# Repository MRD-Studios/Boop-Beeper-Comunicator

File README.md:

# Boop Beeper Comunicator
A Pico Pi & LoRa communicator built on micropython. (The name is not final)

##

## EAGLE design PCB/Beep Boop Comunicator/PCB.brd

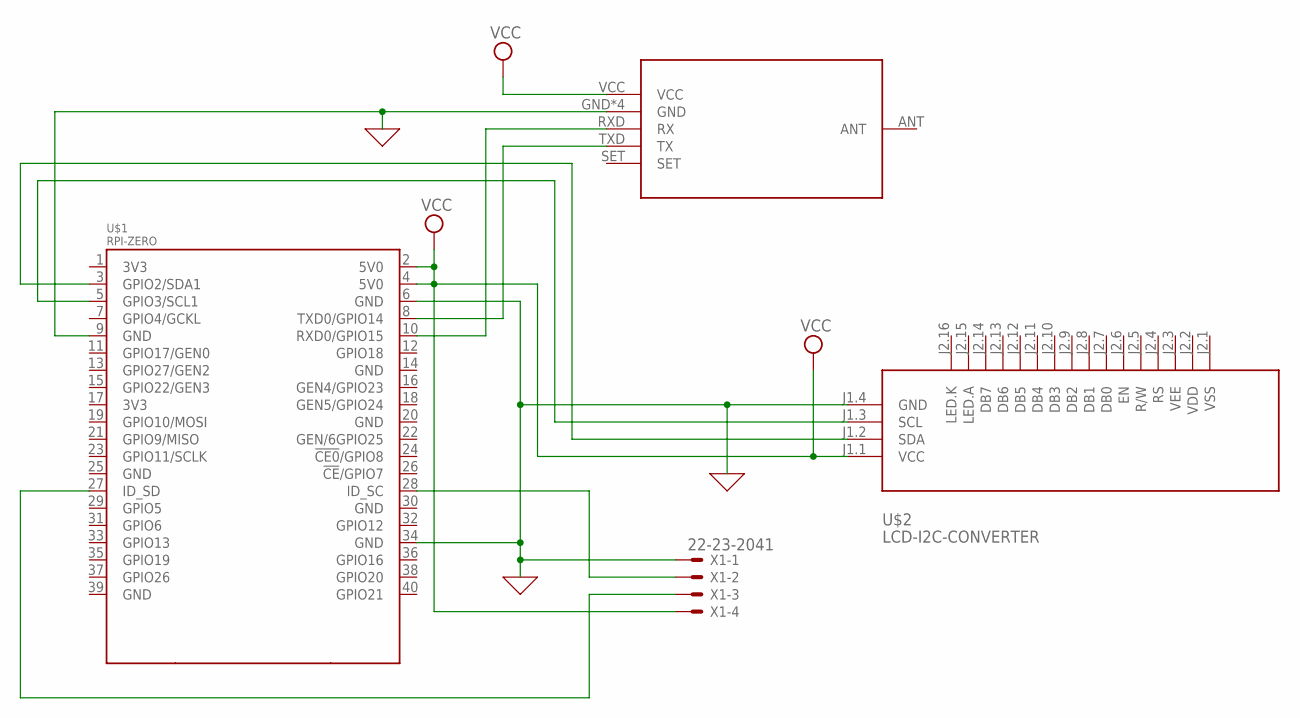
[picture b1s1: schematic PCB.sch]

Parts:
U$1: RPI-ZERO; RASPBERRYPI_BASTELSTUBE_V13_RASPI_BOARD_B+_FULL
U$2: LCD-I2C-CONVERTER
U$3: HC-12
X1: 22-23-2041

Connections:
GND: U$1.6 (GND), U$1.9 (GND), U$1.34 (GND), U$2.J1.4 (GND), U$3.GND, U$3.GND1 (GND), U$3.GND2 (GND), U$3.MCHFIX (GND), X1.1
unnamed: U$1.3 (GPIO2/SDA1), U$2.J1.2 (SDA)
unnamed: U$1.5 (GPIO3/SCL1), U$2.J1.3 (SCL)
unnamed: U$1.8 (TXD0/GPIO14), U$3.TXD (TX)
unnamed: U$1.10 (RXD0/GPIO15), U$3.RXD (RX)
unnamed: U$1.28 (ID_SC), X1.2
unnamed: U$1.27 (ID_SD), X1.3
VCC: U$1.2 (5V0), U$1.4 (5V0), U$2.J1.1 (VCC), U$3.VCC, X1.4

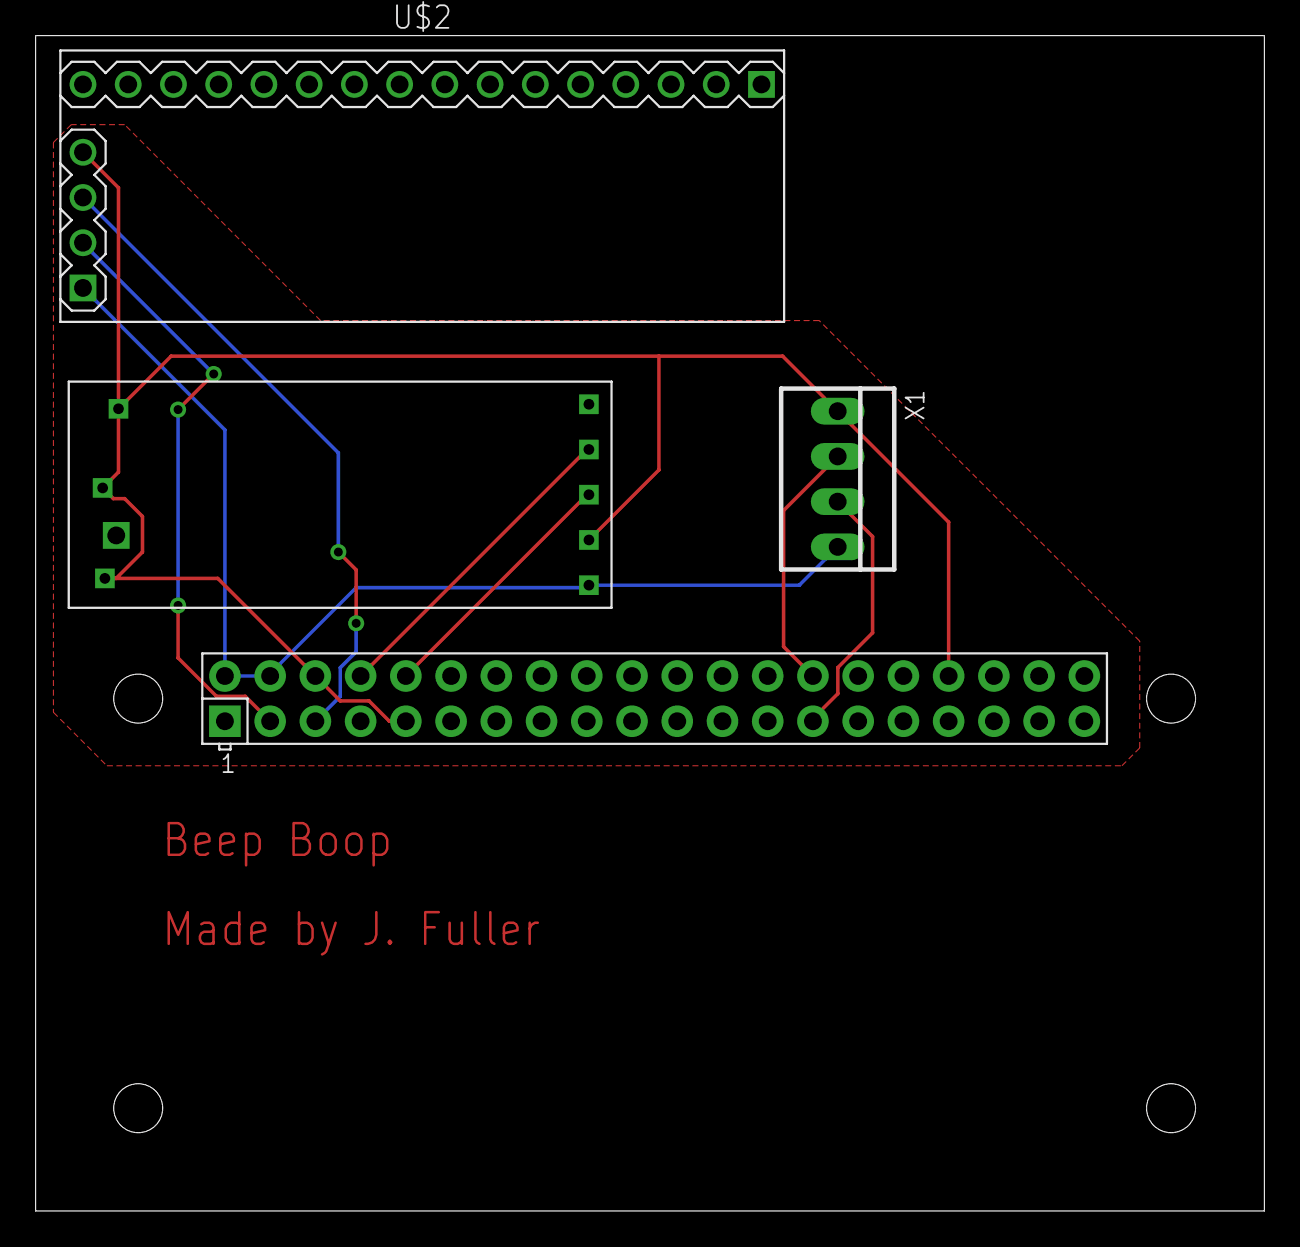
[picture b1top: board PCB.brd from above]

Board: 2 copper layers, 69.0 x 66.0 mm, 4 parts (0 on the bottom side), 8 nets.

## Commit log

2020-09-04 Initial Setup
2020-09-04 Created Parity encoder and check, not working
2020-09-05 Finished Error Check Code
2020-09-05 Created JSON, Setup Encode Message & Error Check
2020-09-05 Encode is naow able to get most of the data needed
2020-09-05 Added Comments, Changed JSON layout, Added Message Encoding
2020-09-05 Added Encryption, Added Ascii to BIN ID converter
2020-09-05 Fixed error caused by unused but needed var
2020-09-05 Added DataCondense which prepares data for sending
2020-09-05 Fixed JSON Reference
2020-09-07 Added PCB and Schematic Design
2020-09-07 Changed Folder, Started Making GUI
2020-09-07 More UI, Added Uptime metadata
2020-09-07 Added Contacts UI and more contacts metadata
2020-09-14 Fully automate dev setup with Gitpod
    This commit implements a fully-automated development setup using Gitpod.io, an
    online IDE for GitHub and GitLab that enables Dev-Environments-As-Code.
    This makes it easy for anyone to get a ready-to-code workspace for any branch,
    issue or pull request almost instantly with a single click.
2021-01-26 Removed gitpod
2021-01-26 Remove Gitpod
2021-01-26 Delete PCB Directory
    Reprogramming for Pico Pi which will require a different PCB
2021-01-26 Removing unwanted cod files for 2.0 rewrite
2021-01-26 Removing unwanted code files for 2.0 rewrite

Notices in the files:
parts and their libraries:
diy-modules: Released under the Creative Commons Attribution 4.0 International License: http://creativecommons.org/licenses/by/4.0
